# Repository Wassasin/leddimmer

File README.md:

# LED PWM dimmer
Quick low-side PWM device to crudely dim two 24V 4A LED strips.

Uses ESP32-C3 LEDC peripheral to provide the PWM signal, and uses two low side gate drivers to pull a N-channel Mosfet. Uses high side current limiters and fuses as protection.

## TODO
* 100K Pull-up esp32 enable
* 100K Pull-downs for drv-enable
* 47nF filter voor isense
* Swap drv2 isense en drvsense
* WS2812B data line on 3V3
* Status line high side driver useless without output voltages
* Caps C5750X7R1V476M230KC / 47uF 35V X7R 2220

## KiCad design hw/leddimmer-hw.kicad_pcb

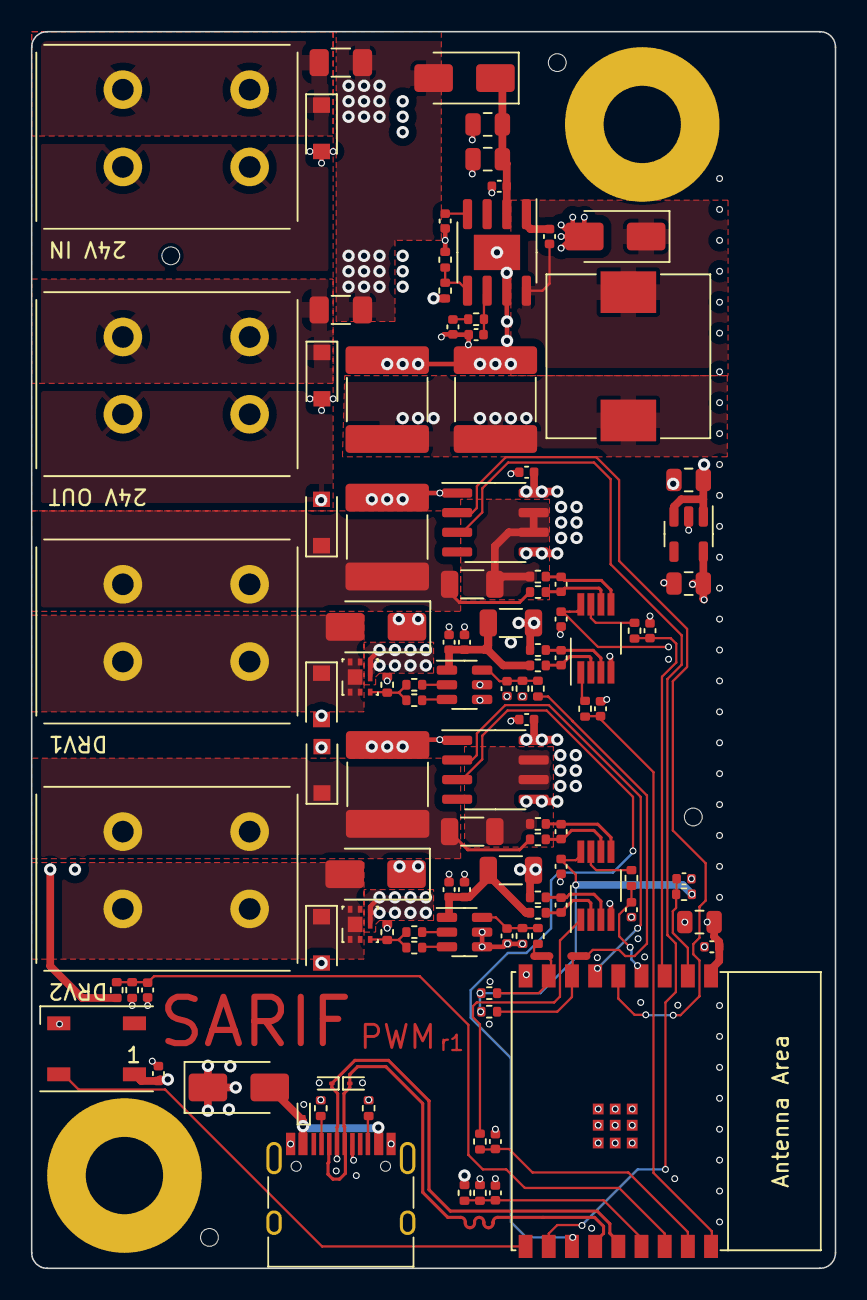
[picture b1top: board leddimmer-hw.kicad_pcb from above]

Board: 4 copper layers, 52.0 x 80.0 mm, 117 parts (0 on the bottom side), 62 nets.

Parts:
C201, C204, C210, C301, C304, C310, C509, C601, C603, C604, C605, C606: 100nF; C_0402_1005Metric
C202, C205, C206, C302, C305, C306: C_0402_1005Metric
C203, C303, C505: 1uF; C_0402_1005Metric
C207, C307, C510, C511: 47uF; C_2220_5750Metric
C208, C209, C308, C309, C501: 6.8nF; C_0402_1005Metric
C502, C504, C602: 10uF; C_0805_2012Metric
C503: 220pF; C_0402_1005Metric
C506: 8.2nF; C_0402_1005Metric
C507, C508: 10u; C_0805_2012Metric
D201, D301, D501, D502, D503: SS54; D_SMA
D401: ESD9X5.0ST5G; D_SOD-923
D402, D403: ESD9L3.3ST5G; D_SOD-923
D404, D405, D406, D407, D408, D409: SJD12A28L01; D_SOD-123S
D601: WS2812B; LED_WS2812B_PLCC4_5.0x5.0mm_P3.2mm
F401, F402: 0501010.WR1; Fuse_1206_3216Metric
H101, H102, H103, H104: ToolingHole; JLCPCB tooling hole
H105, H106: MountingHole; MountingHole_5mm_Keepout
J401, J402, J403, J404: 2604-1102; WAGO-2604-1102
L501: SDSL10D40F-3R8Y; L_10.4x10.4_H4.8
NT601, NT602: NetTie_2; NetTie-2_SMD_Pad0.5mm
P401: TYPE-C-31-M-12; USB_C_Receptacle_HRO_TYPE-C-31-M-12
Q201, Q301: CSD17571Q2
R201, R203, R204, R207, R208, R209, R210, R301, R303, R304, R307, R308, R309, R310: 1Ohm; R_0402_1005Metric
R202, R211, R302, R311, R601, R602, R603, R604, R606: 100kOhm; R_0402_1005Metric
R205, R206, R305, R306: 3mR 1%; R_1206_3216Metric
R212, R213, R312, R313, R401, R402: 5.1kOhm; R_0402_1005Metric
R501: 121kOhm; R_0402_1005Metric
R502, R607: 10.2kOhm; R_0402_1005Metric
R503, R605: 1.96kOhm; R_0402_1005Metric
U201, U301: NCV8460A; SOIC-8_3.9x4.9mm_P1.27mm
U202, U302: UCC27511DBVR; SOT-23-6
U203, U303: INA2180A2IDGKR; VSSOP-8_3.0x3.0mm_P0.65mm
U501: TPS54332DDAR; SOIC-8-1EP_3.9x4.9mm_P1.27mm_EP2.29x3mm
U502: AP2112K-3.3; SOT-23-5
U601: ESP32-C3-WROOM-02

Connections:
+3V3: C210.1, C310.1, C508.1, C602.1, C603.1, R601.2, R602.2, R603.2, U203.8 (VS), U303.8 (VS), U502.5 (VOUT), U601.1 (3V3)
+5V: C507.1, C510.1, C511.1, C604.1, D502.1 (K), D601.1 (VDD), L501.2, R205.1, R207.2, R305.1, R307.2, R502.2, R606.2, U502.1 (VIN), U502.3 (EN)
+24V: C201.1, C301.1, D201.1 (K), D301.1 (K), D501.2 (A), F401.1, F402.1, R604.2, U201.5 (VD), U201.8 (VD), U301.5 (VD), U301.8 (VD)
/Connectors/24V_1: D404.1 (K), F401.2, J401.1
/Connectors/24V_2: D409.1 (K), F402.2, J404.1
/Connectors/DRV1+: C207.1, D405.1 (K), J402.1, R206.1, R210.2
/Connectors/DRV1-: D201.2 (A), D407.1 (K), J402.2, Q201.1 (D)
/Connectors/DRV2+: C307.1, D406.1 (K), J403.1, R306.1, R310.2
/Connectors/DRV2-: D301.2 (A), D408.1 (K), J403.2, Q301.1 (D)
/Connectors/USB_CC1: P401.A5 (CC1), R401.1
/Connectors/USB_CC2: P401.B5 (CC2), R402.1
/Connectors/USB_D+: D403.1 (K), P401.A6 (D+), P401.B6 (D+), U601.14 (GPIO19/USB_D+)
/Connectors/USB_D-: D402.1 (K), P401.A7 (D-), P401.B7 (D-), U601.13 (GPIO18/USB_D-)
/Driver 1/24V_SWITCHED: R204.2, R206.2, U201.6 (OUT), U201.7 (OUT)
/Driver 1/+5V_DRV: C203.1, C204.1, R203.2, R205.2, U202.1 (V_{DD})
/Driver 1/DRVMON: C209.1, R213.2, U601.18 (GPIO0/ADC1_CH0/XTAL_32K_P)
/Driver 1/DRVSENSE: R213.1, U203.1 (OUT1)
/Driver 1/DRVSENSE+: C205.2, R207.1, U203.3 (IN+1)
/Driver 1/DRVSENSE-: C205.1, R203.1, U203.2 (IN-1)
/Driver 1/ENABLE: U201.2 (IN), U601.5 (GPIO6)
/Driver 1/GATE: Q201.2 (G), R208.2, R209.1, R211.2
/Driver 1/GATEH: R208.1, U202.2 (OUTH)
/Driver 1/GATEL: R209.2, U202.3 (OUTL)
/Driver 1/IMON: C208.1, R212.2, U601.3 (GPIO4/ADC1_CH4)
/Driver 1/ISENSE: R212.1, U203.7 (OUT2)
/Driver 1/ISENSE+: C206.1, R204.1, U203.5 (IN+2)
/Driver 1/ISENSE-: C206.2, R210.1, U203.6 (IN-2)
/Driver 1/PWM: NT601.2, R201.1
/Driver 1/PWM_FILT: C202.1, R201.2, R202.2, U202.6 (IN+)
/Driver 1/STAT: U201.3 (STAT), U601.11 (GPIO20/U0RXD)
/Driver 2/24V_SWITCHED: R304.2, R306.2, U301.6 (OUT), U301.7 (OUT)
/Driver 2/+5V_DRV: C303.1, C304.1, R303.2, R305.2, U302.1 (V_{DD})
/Driver 2/DRVMON: C309.1, R313.2, U601.17 (GPIO1/ADC1_CH1/XTAL_32K_N)
/Driver 2/DRVSENSE: R313.1, U303.1 (OUT1)
/Driver 2/DRVSENSE+: C305.2, R307.1, U303.3 (IN+1)
/Driver 2/DRVSENSE-: C305.1, R303.1, U303.2 (IN-1)
/Driver 2/ENABLE: U301.2 (IN), U601.6 (GPIO7)
/Driver 2/GATE: Q301.2 (G), R308.2, R309.1, R311.2
/Driver 2/GATEH: R308.1, U302.2 (OUTH)
/Driver 2/GATEL: R309.2, U302.3 (OUTL)
/Driver 2/IMON: C308.1, R312.2, U601.4 (GPIO5/ADC2_CH0)
/Driver 2/ISENSE: R312.1, U303.7 (OUT2)
/Driver 2/ISENSE+: C306.1, R304.1, U303.5 (IN+2)
/Driver 2/ISENSE-: C306.2, R310.1, U303.6 (IN-2)
/Driver 2/PWM: NT602.2, R301.1
/Driver 2/PWM_FILT: C302.1, R301.2, R302.2, U302.6 (IN+)
/Driver 2/STAT: U301.3 (STAT), U601.12 (GPIO21/U0TXD)
/MCU/5V_MEAS: C606.1, R606.1, R607.2, U601.15 (GPIO3/ADC1_CH3)
/MCU/24V_MEAS: C605.1, R604.1, R605.2, U601.16 (GPIO2/ADC1_CH2)
/MCU/EN: C601.1, R603.1, U601.2 (EN/CHIP_PU)
/MCU/IO8_STRAP: NT601.1, R601.1, U601.7 (GPIO8)
/MCU/IO9_STRAP: NT602.1, R602.1, U601.8 (GPIO9)
/MCU/LED: D601.4 (DIN), U601.10 (GPIO10)
/Power/5V_BOOT: C509.2, U501.1 (BOOT)
/Power/5V_COMP: C501.1, R501.2, U501.6 (COMP)
/Power/5V_PH: C509.1, D503.1 (K), L501.1, U501.8 (PH)
/Power/5V_SS: C506.1, U501.4 (SS)
/Power/5V_VSENSE: R502.1, R503.2, U501.5 (VSENSE)
/Power/24V_FILT: C502.1, C504.1, C505.1, D501.1 (K), U501.2 (VIN)
GND: C201.2, C202.2, C203.2, C204.2, C207.2, C208.2, C209.2, C210.2, C301.2, C302.2, C303.2, C304.2, C307.2, C308.2, C309.2, C310.2, C501.2, C502.2, C503.2, C504.2, C505.2, C506.2, C507.2, C508.2, C510.2, C511.2, C601.2, C602.2, C603.2, C604.2, C605.2, C606.2, D401.2 (A), D402.2 (A), D403.2 (A), D404.2 (A), D405.2 (A), D406.2 (A), D407.2 (A), D408.2 (A), D409.2 (A), D503.2 (A), D601.3 (VSS), J401.2, J404.2, P401.A1 (GND), P401.A12 (GND), P401.B1 (GND), P401.B12 (GND), P401.S1 (SHIELD), Q201.3 (S), Q301.3 (S), R202.1, R211.1, R302.1, R311.1, R401.2, R402.2, R503.1, R605.1, R607.1, U201.1 (GND), U202.4 (GND), U202.5 (IN-), U203.4 (GND), U301.1 (GND), U302.4 (GND), U302.5 (IN-), U303.4 (GND), U501.7 (GND), U501.9 (GND), U502.2 (GND), U601.9 (GND), U601.19 (GND)
unnamed: C503.1, R501.1
VBUS: D401.1 (K), D502.2 (A), P401.A4 (VBUS), P401.A9 (VBUS), P401.B4 (VBUS), P401.B9 (VBUS)

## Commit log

2023-11-20 Sent rev1 to factory
2024-01-18 Fixed some bugs
2024-01-18 Added lock file to .gitignore
2024-01-18 Removed R{1,2}02 pull-down because it ruins strap
2024-02-19 Initial firmware
2024-02-19 Committed flake
2024-02-19 Reworked ADC imon line
2024-02-19 WIP partitions and LED controller
2024-02-27 Progress on adding power control
2024-02-27 Implemented power fault lockout
2024-02-28 Removed fault from enabled
2024-02-29 Implemented emotes
